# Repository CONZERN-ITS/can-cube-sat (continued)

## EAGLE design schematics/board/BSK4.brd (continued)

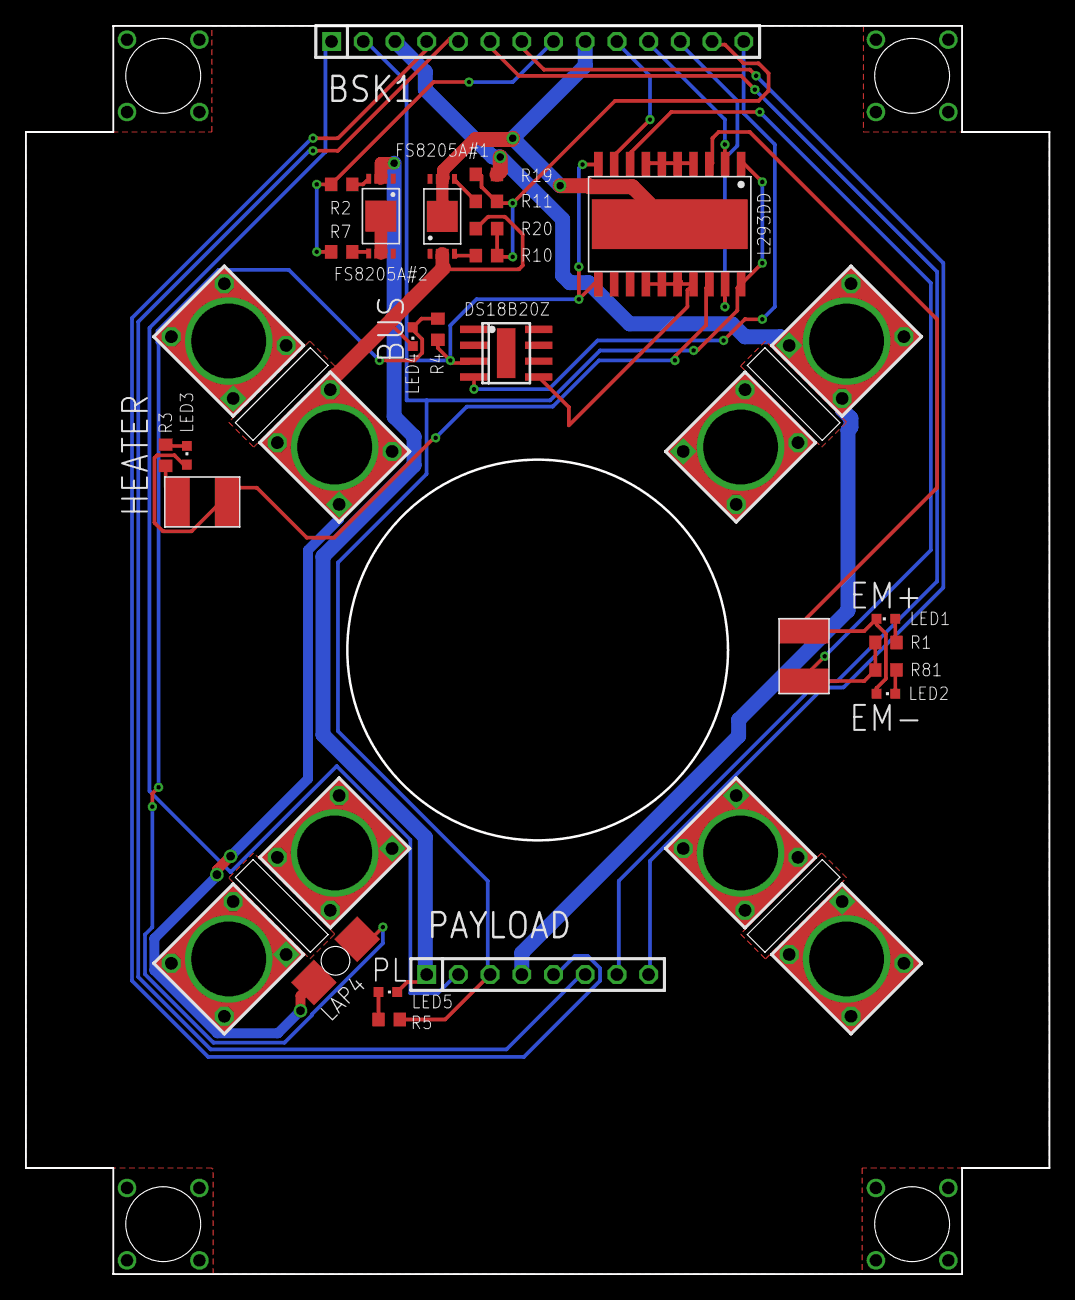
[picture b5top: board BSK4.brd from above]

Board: 2 copper layers, 82.0 x 100.0 mm, 33 parts (0 on the bottom side), 34 nets.

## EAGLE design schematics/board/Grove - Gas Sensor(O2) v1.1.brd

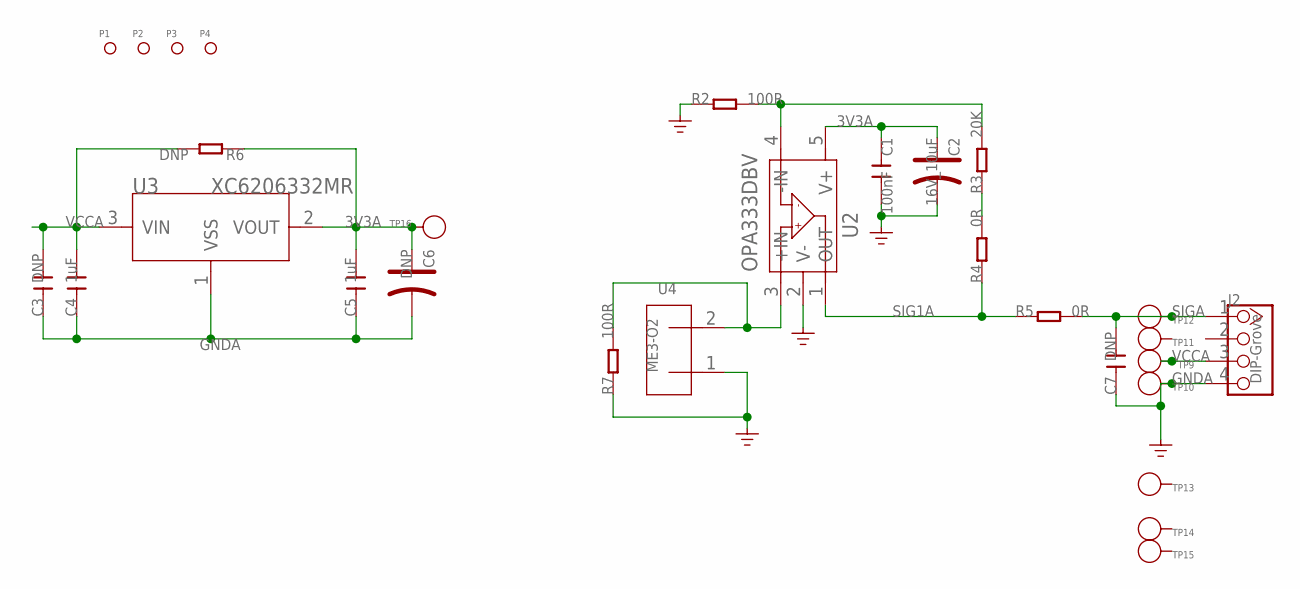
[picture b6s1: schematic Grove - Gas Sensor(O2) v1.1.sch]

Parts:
C1: 100nF; C0603
C2: 16V_10uF; AVX-A
C3, C7: DNP; C0805
C4, C5: 1uF; C0603
C6: DNP; AVX-A
J2: DIP-Grove; 4P-2.0
P1, P2, P3, P4: PAD-MARK'ANNULAR'; ROUND-MARK-1.0
R2, R7: 100R; R0603
R3: 20K; R0603
R4, R5: 0R; R0603
R6: DNP; R0603
TP9, TP10, TP11, TP12, TP13, TP14, TP15, TP16: PAD-TEST-POINT'4545'; TP_4545
U2: OPA333DBV; SOT23-5
U3: XC6206332MR; SOT23
U4: ME3-O2; 2P-D20X16H

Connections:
3V3A: C1.1, C2.+, C5.2, C6.+, R6.1, TP16.T, U2.5 (V+), U3.2 (VOUT)
GNDA: C1.2, C2.-, C3.1, C4.1, C5.1, C6.-, C7.1, J2.4, R2.1, R7.1, TP10.T, U2.2 (V-), U3.1 (VSS), U4.1
unnamed: R7.2, U2.3 (+IN), U4.2
unnamed: R2.2, R3.2, U2.4 (-IN)
unnamed: R3.1, R4.2
SIG1A: R4.1, R5.1, U2.1 (OUT)
SIGA: C7.2, J2.1, R5.2, TP12.T
VCCA: C3.2, C4.2, J2.3, R6.2, TP9.T, U3.3 (VIN)

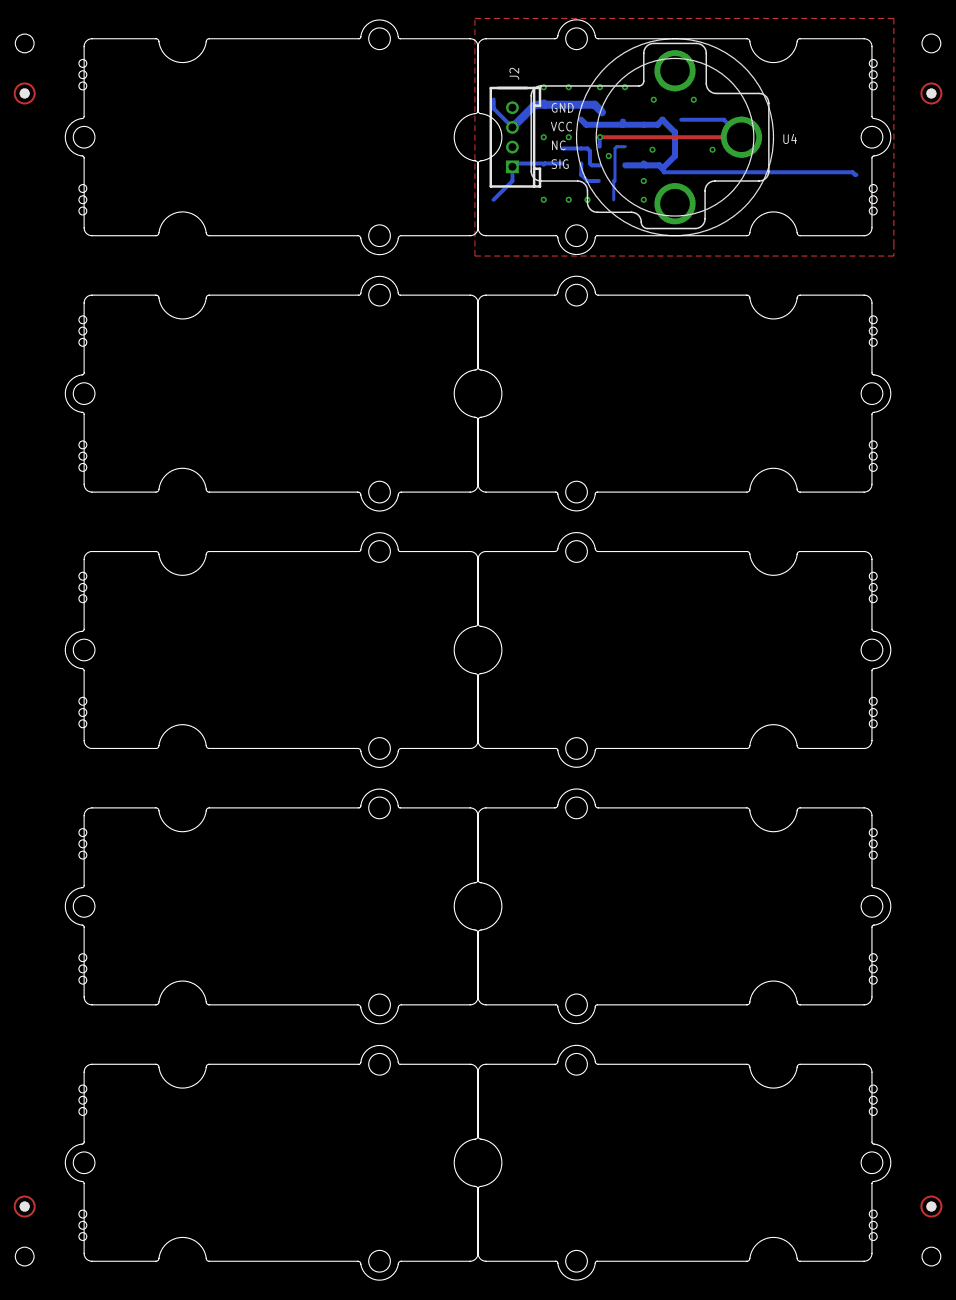
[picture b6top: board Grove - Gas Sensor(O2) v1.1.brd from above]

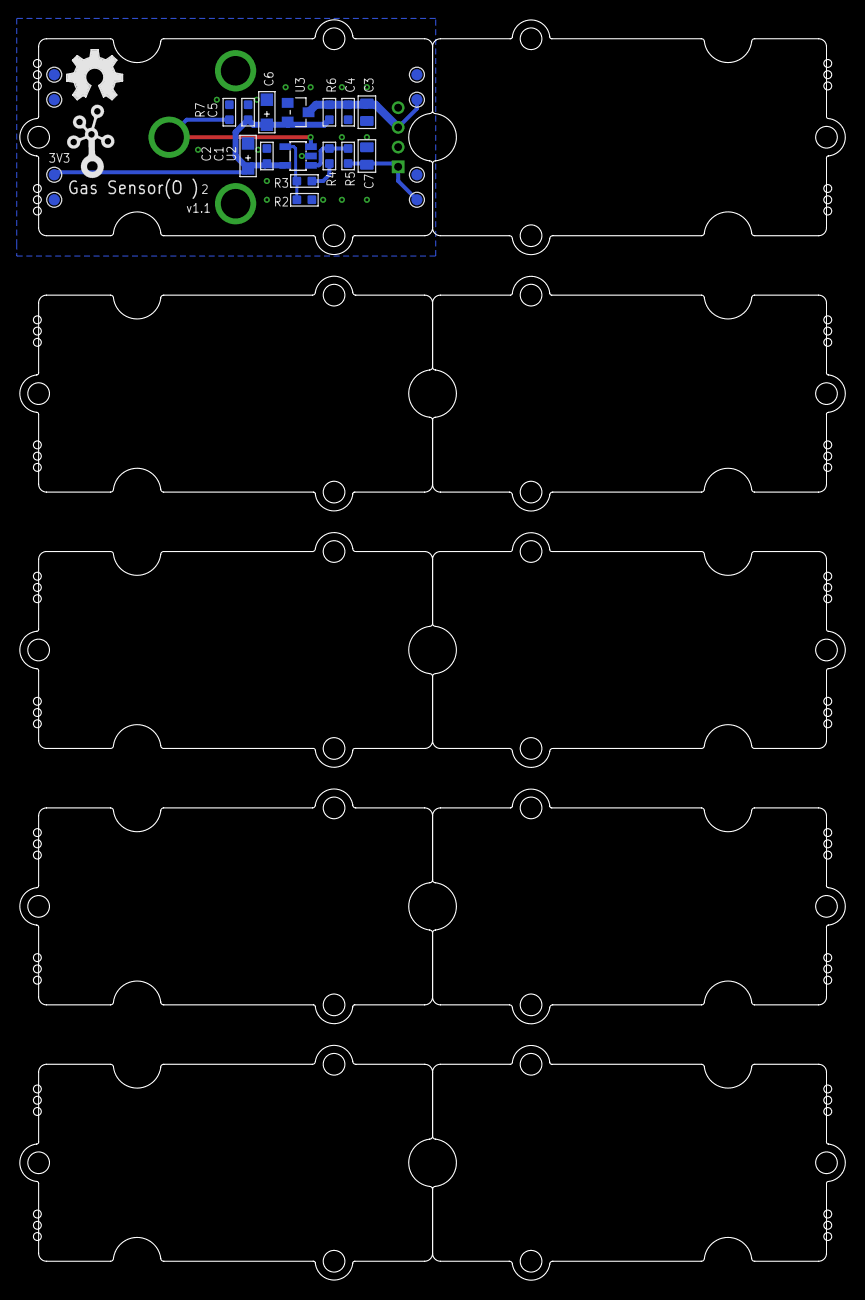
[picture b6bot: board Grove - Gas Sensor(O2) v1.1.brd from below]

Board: 2 copper layers, 83.8 x 128.0 mm, 41 parts (25 on the bottom side), 8 nets.

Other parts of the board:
U$1, U$2, U$3, U$4, U$5, U$6, U$8, U$14, U$16, U$18: GROVE-TEST-PLATFORM
U$15: OSHW_FILLX200_NOTEXT
U$17: TWIGLOGO
